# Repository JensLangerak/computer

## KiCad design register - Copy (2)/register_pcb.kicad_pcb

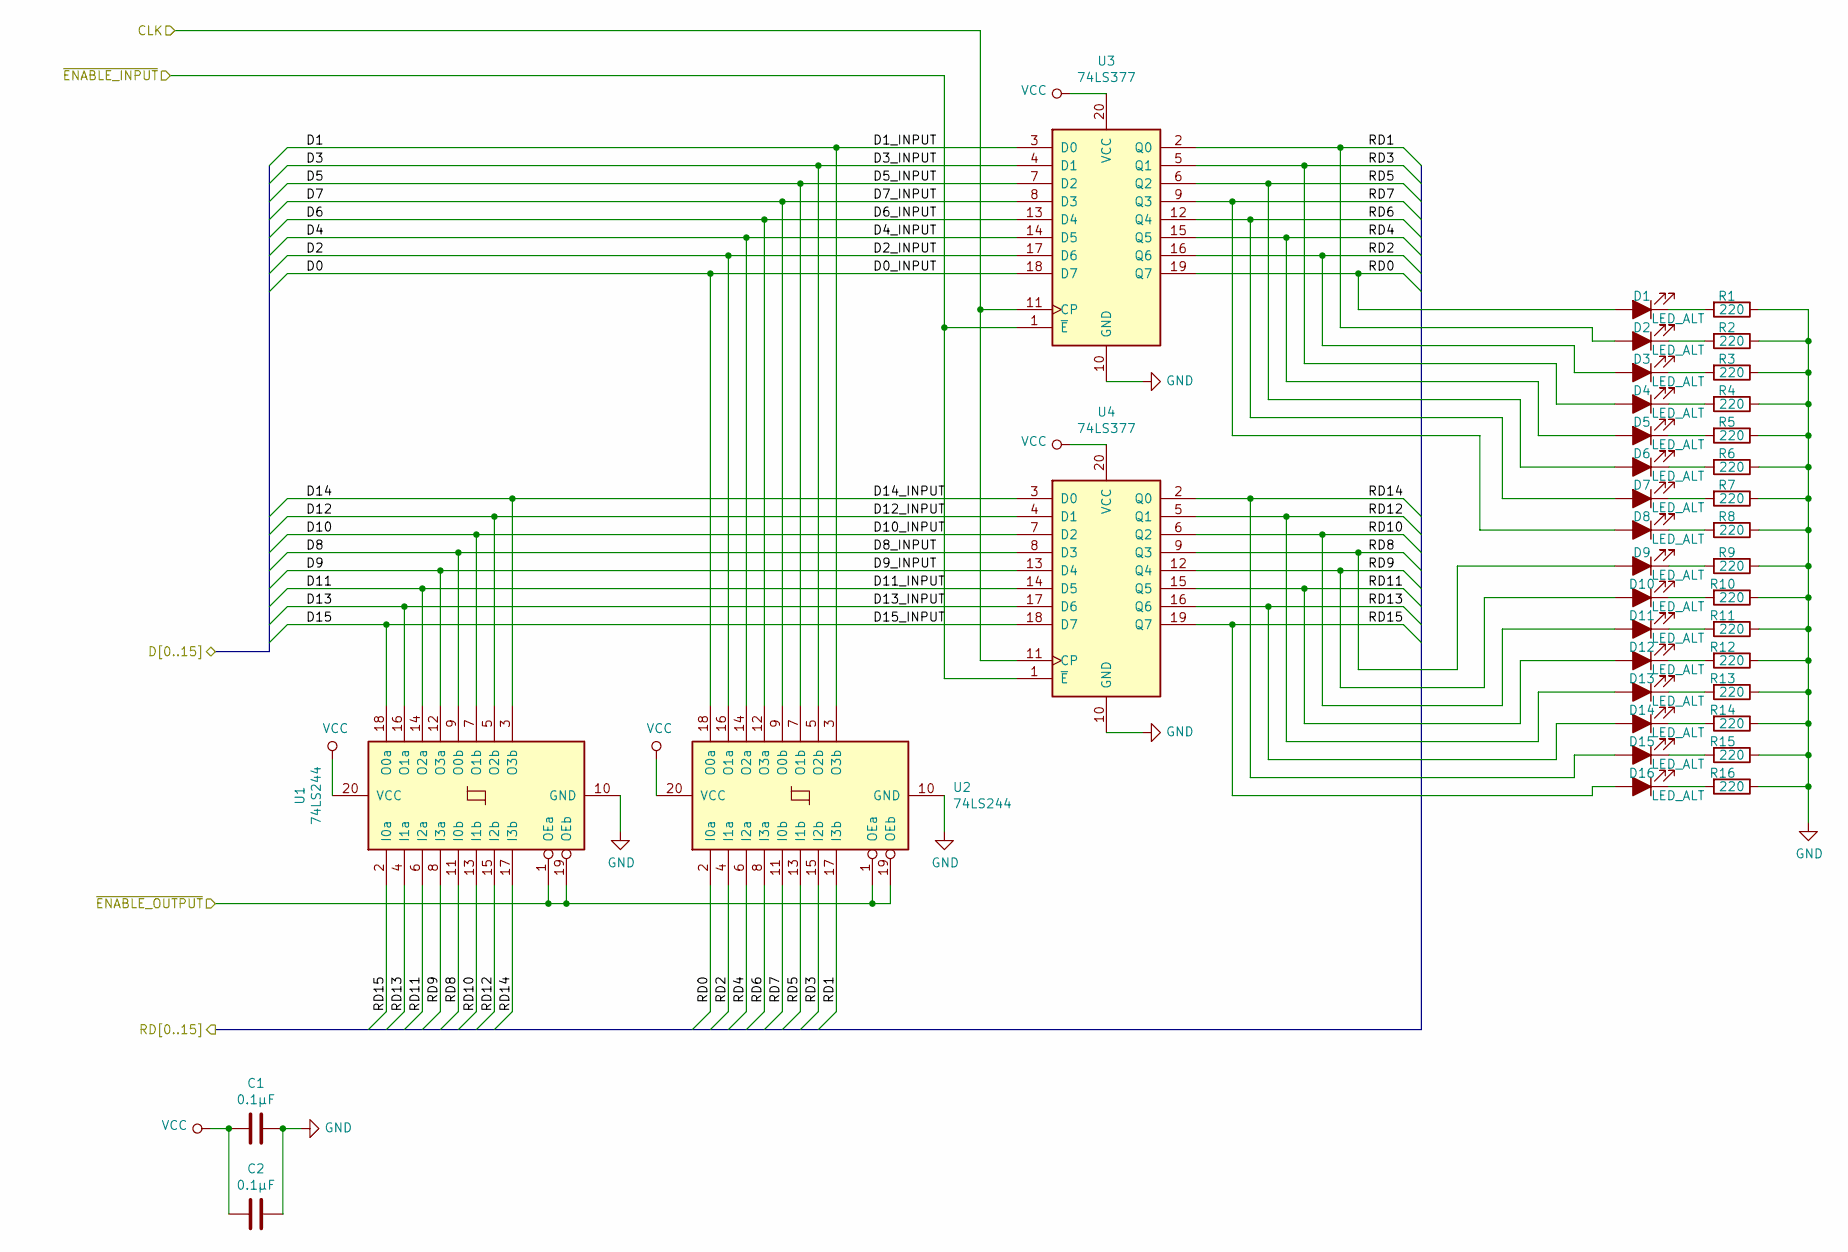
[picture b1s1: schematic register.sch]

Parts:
C1, C2: 0.1µF; C_Disc_D4.3mm_W1.9mm_P5.00mm
D1, D2, D3, D4, D5, D6, D7, D8, D9, D10, D11, D12, D13, D14, D15, D16: LED_ALT; LED_D5.0mm
R1, R2, R3, R4, R5, R6, R7, R8, R9, R10, R11, R12, R13, R14, R15, R16: 220; R_Axial_DIN0207_L6.3mm_D2.5mm_P7.62mm_Horizontal
U1, U2: 74LS244; DIP-20_W7.62mm_LongPads
U3, U4: 74LS377; DIP-20_W7.62mm_LongPads

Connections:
/CLK: U3.11 (CP), U4.11 (CP); also elsewhere on the board
/D0: U2.18 (O0a), U3.18 (D7); also elsewhere on the board
/D1: U2.3 (O3b), U3.3 (D0); also elsewhere on the board
/D2: U2.16 (O1a), U3.17 (D6); also elsewhere on the board
/D3: U2.5 (O2b), U3.4 (D1); also elsewhere on the board
/D4: U2.14 (O2a), U3.14 (D5); also elsewhere on the board
/D5: U2.7 (O1b), U3.7 (D2); also elsewhere on the board
/D6: U2.12 (O3a), U3.13 (D4); also elsewhere on the board
/D7: U2.9 (O0b), U3.8 (D3); also elsewhere on the board
/D8: U1.9 (O0b), U4.8 (D3); also elsewhere on the board
/D9: U1.12 (O3a), U4.13 (D4); also elsewhere on the board
/D10: U1.7 (O1b), U4.7 (D2); also elsewhere on the board
/D11: U1.14 (O2a), U4.14 (D5); also elsewhere on the board
/D12: U1.5 (O2b), U4.4 (D1); also elsewhere on the board
/D13: U1.16 (O1a), U4.17 (D6); also elsewhere on the board
/D14: U1.3 (O3b), U4.3 (D0); also elsewhere on the board
/D15: U1.18 (O0a), U4.18 (D7); also elsewhere on the board
/RD0: D1.2 (A), U2.2 (I0a), U3.19 (Q7); also elsewhere on the board
/RD1: D2.2 (A), U2.17 (I3b), U3.2 (Q0); also elsewhere on the board
/RD2: D3.2 (A), U2.4 (I1a), U3.16 (Q6); also elsewhere on the board
/RD3: D4.2 (A), U2.15 (I2b), U3.5 (Q1); also elsewhere on the board
/RD4: D5.2 (A), U2.6 (I2a), U3.15 (Q5); also elsewhere on the board
/RD5: D6.2 (A), U2.13 (I1b), U3.6 (Q2); also elsewhere on the board
/RD6: D7.2 (A), U2.8 (I3a), U3.12 (Q4); also elsewhere on the board
/RD7: D8.2 (A), U2.11 (I0b), U3.9 (Q3); also elsewhere on the board
/RD8: D9.2 (A), U1.11 (I0b), U4.9 (Q3); also elsewhere on the board
/RD9: D10.2 (A), U1.8 (I3a), U4.12 (Q4); also elsewhere on the board
/RD10: D11.2 (A), U1.13 (I1b), U4.6 (Q2); also elsewhere on the board
/RD11: D12.2 (A), U1.6 (I2a), U4.15 (Q5); also elsewhere on the board
/RD12: D13.2 (A), U1.15 (I2b), U4.5 (Q1); also elsewhere on the board
/RD13: D14.2 (A), U1.4 (I1a), U4.16 (Q6); also elsewhere on the board
/RD14: D15.2 (A), U1.17 (I3b), U4.2 (Q0); also elsewhere on the board
/RD15: D16.2 (A), U1.2 (I0a), U4.19 (Q7); also elsewhere on the board
/~ENABLE_INPUT~: U3.1 (~E), U4.1 (~E); also elsewhere on the board
/~ENABLE_OUTPUT~: U1.1 (OEa), U1.19 (OEb), U2.1 (OEa), U2.19 (OEb); also elsewhere on the board
GND: C1.2, C2.2, R1.1, R2.1, R3.1, R4.1, R5.1, R6.1, R7.1, R8.1, R9.1, R10.1, R11.1, R12.1, R13.1, R14.1, R15.1, R16.1, U1.10 (GND), U2.10 (GND), U3.10 (GND), U4.10 (GND); also elsewhere on the board
unnamed: D1.1 (K), R1.2
unnamed: D2.1 (K), R2.2
unnamed: D3.1 (K), R3.2
unnamed: D4.1 (K), R4.2
unnamed: D5.1 (K), R5.2
unnamed: D6.1 (K), R6.2
unnamed: D7.1 (K), R7.2
unnamed: D8.1 (K), R8.2
unnamed: D9.1 (K), R9.2
unnamed: D10.1 (K), R10.2
unnamed: D11.1 (K), R11.2
unnamed: D12.1 (K), R12.2
unnamed: D13.1 (K), R13.2
unnamed: D14.1 (K), R14.2
unnamed: D15.1 (K), R15.2
unnamed: D16.1 (K), R16.2
VCC: C1.1, C2.1, U1.20 (VCC), U2.20 (VCC), U3.20 (VCC), U4.20 (VCC); also elsewhere on the board

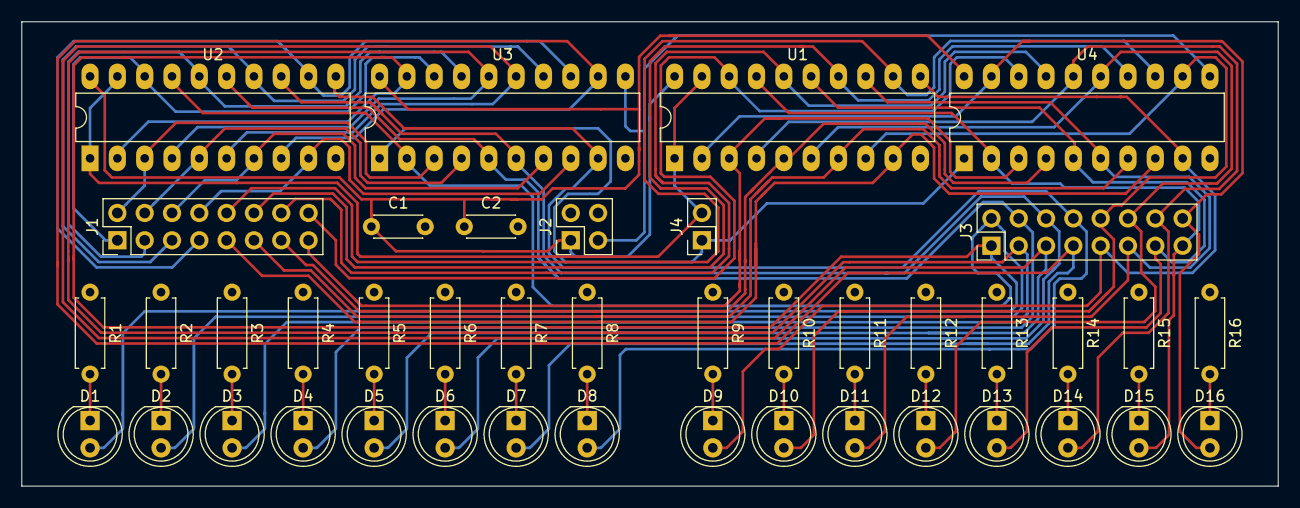
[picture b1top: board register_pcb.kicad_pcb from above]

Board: 2 copper layers, 116.8 x 43.2 mm, 42 parts (0 on the bottom side), 53 nets.

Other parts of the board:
J1, J3: Conn_02x08_Odd_Even; PinHeader_2x08_P2.54mm_Vertical
J2: Conn_02x02_Odd_Even; PinHeader_2x02_P2.54mm_Vertical
J4: Conn_02x01; PinHeader_2x01_P2.54mm_Vertical

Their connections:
/CLK: J2.3; also elsewhere on the board
/D0: J1.1; also elsewhere on the board
/D1: J1.2; also elsewhere on the board
/D2: J1.3; also elsewhere on the board
/D3: J1.4; also elsewhere on the board
/D4: J1.5; also elsewhere on the board
/D5: J1.6; also elsewhere on the board
/D6: J1.7; also elsewhere on the board
/D7: J1.8; also elsewhere on the board
/D8: J1.9; also elsewhere on the board
/D9: J1.10; also elsewhere on the board
/D10: J1.11; also elsewhere on the board
/D11: J1.12; also elsewhere on the board
/D12: J1.13; also elsewhere on the board
/D13: J1.14; also elsewhere on the board
/D14: J1.15; also elsewhere on the board
/D15: J1.16; also elsewhere on the board
/RD0: J3.1; also elsewhere on the board
/RD1: J3.2; also elsewhere on the board
/RD2: J3.3; also elsewhere on the board
/RD3: J3.4; also elsewhere on the board
/RD4: J3.5; also elsewhere on the board
/RD5: J3.6; also elsewhere on the board
/RD6: J3.7; also elsewhere on the board
/RD7: J3.8; also elsewhere on the board
/RD8: J3.9; also elsewhere on the board
/RD9: J3.10; also elsewhere on the board
/RD10: J3.11; also elsewhere on the board
/RD11: J3.12; also elsewhere on the board
/RD12: J3.13; also elsewhere on the board
/RD13: J3.14; also elsewhere on the board
/RD14: J3.15; also elsewhere on the board
/RD15: J3.16; also elsewhere on the board
/~ENABLE_INPUT~: J4.1; also elsewhere on the board
/~ENABLE_OUTPUT~: J4.2; also elsewhere on the board
GND: J2.2; also elsewhere on the board
VCC: J2.1; also elsewhere on the board
